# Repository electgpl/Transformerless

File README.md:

# Fuente sin Transformador Transformerless

Este es un proyecto muy simple para alimentar circuitos donde no se requieren corriente altas y donde no se requiere un nivel bajo de ruido.
El circuito esta basado en la nota de aplicación de Microchip AN954

## Propiedades

  - Bajo nivel de Eficiencia
  - Alto nivel de factor de risado o ripple
  - Baja corriente de salida
  - Baja disipación de calor
  - Bajo costo
  - Muy pocos componentes

## Alimentación

> Diseñado para trabajar hasta 220Vac y 50Hz, cualquier otro valor se debe tener en cuenta al momento de calcular el capacitor de entrada.

### Diseño

> Diseñado con EAGLE, en solo dos capas con componentes THT para facilitar
> la integración al alumno, el desarrollo del PCB en el hogar y mantener
> el menor costo posible.

### Análisis en LTSpice

## License

The MIT License (MIT) - see [`LICENSE.md`](https://github.com/fatih/color/blob/master/LICENSE.md) for more details

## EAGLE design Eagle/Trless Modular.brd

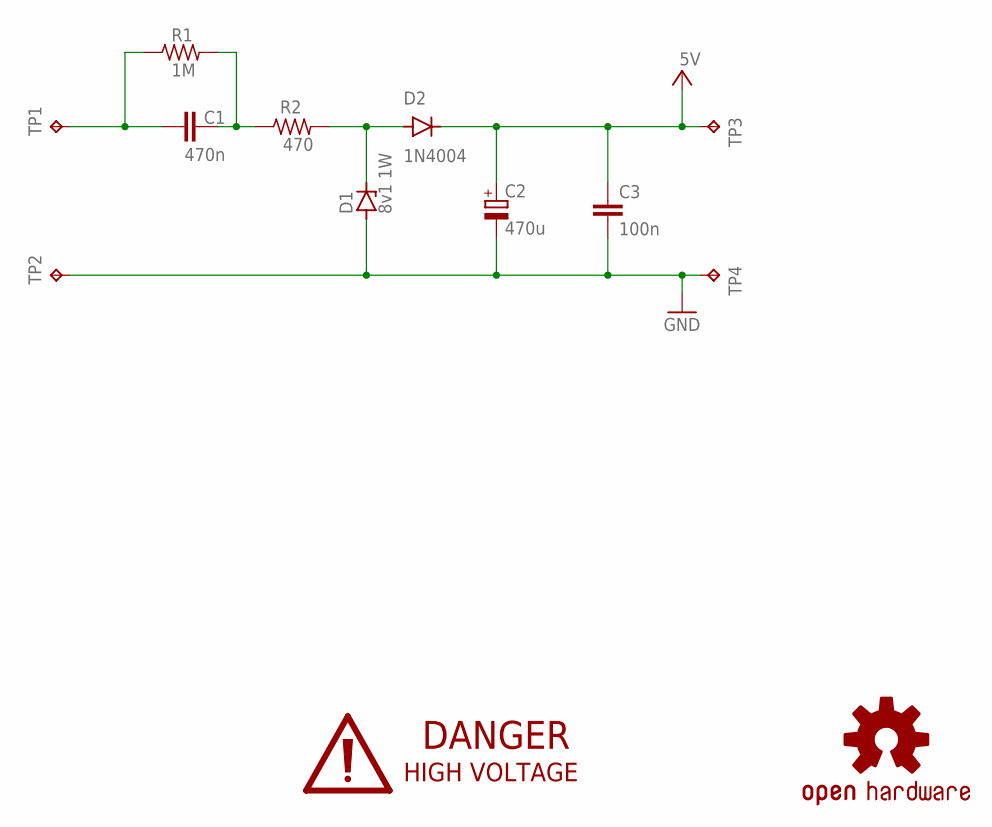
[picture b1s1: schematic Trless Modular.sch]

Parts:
C1: 470n; C150-054X183
C2: 470u; E3,5-8
C3: 100n; C050-024X044
D1: 8v1 1W; DO35Z10
D2: 1N4004; DO41-10
L2: OSHW-LOGOS; OSHW-LOGO-S
R1: 1M; 0207/10
R2: 470; 0207/10
TP1, TP2, TP3, TP4: TPPAD1-17; P1-17

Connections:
+3V3: C2.+, C3.1, D2.C, TP3.TP
GND: C2.-, C3.2, D1.A, TP2.TP, TP4.TP
LINE: C1.1, R1.1, TP1.TP
unnamed: C1.2, R1.2, R2.1
unnamed: D1.C, D2.A, R2.2

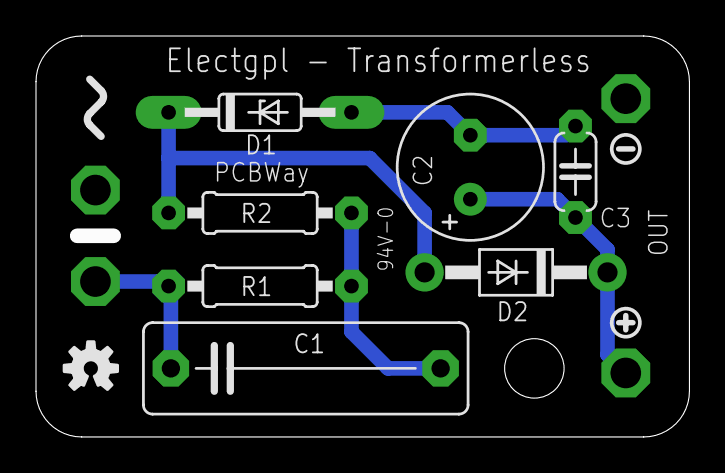
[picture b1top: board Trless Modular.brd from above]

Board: 2 copper layers, 35.5 x 21.5 mm, 15 parts (0 on the bottom side), 5 nets.

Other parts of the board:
U$1: ICON_AC
U$2: ICON_MINUS
U$3: ICON_PLUS

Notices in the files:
parts and their libraries:
dicons: Copyright (C) 2004, Bob Starr (rtzaudio@mindspring.com)
SparkFun-Aesthetics: Licensing: CC v3.0 Share-Alike You are welcome to use this library for commercial purposes.
dsymbols: Copyright (C) 2005, Bob Starr (bobstarr@mindspring.com)
